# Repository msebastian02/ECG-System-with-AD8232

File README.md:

# ECG-System-with-AD8232

ECG System with STM32F405RGT and AD8232

The system is an interface between an AD8232 and a MCU STM32F405 used to processing, encryption and sending electrocardiography data to a remote server via wifi.

This part was created in Eagle .

Repository Contents

1. Hardware - All Eagle design files (.brd, .sch)

2. Software - MCU Code & WebPageInterface

\*MCU Code - Written and compiled in Keil uVision v5.29

\*WebPageInterface - FrontEnd Written and compiled in Angular 8+ Framework &amp;amp; BackEnd Written and compiled in Python Flask

\*ESP01 Code - Written and compiled in Arduino IDE

3.Documentation

Monograph of the degree project related to the project

Version History

v1.0 Initial Release

License Information

The hardware and code was developed by:

\*Juan Sebastian Munar Aldana

\*Carlos Eduardo Moreno Doria

Electronic engineers from Santo Tomas university, Bogota.

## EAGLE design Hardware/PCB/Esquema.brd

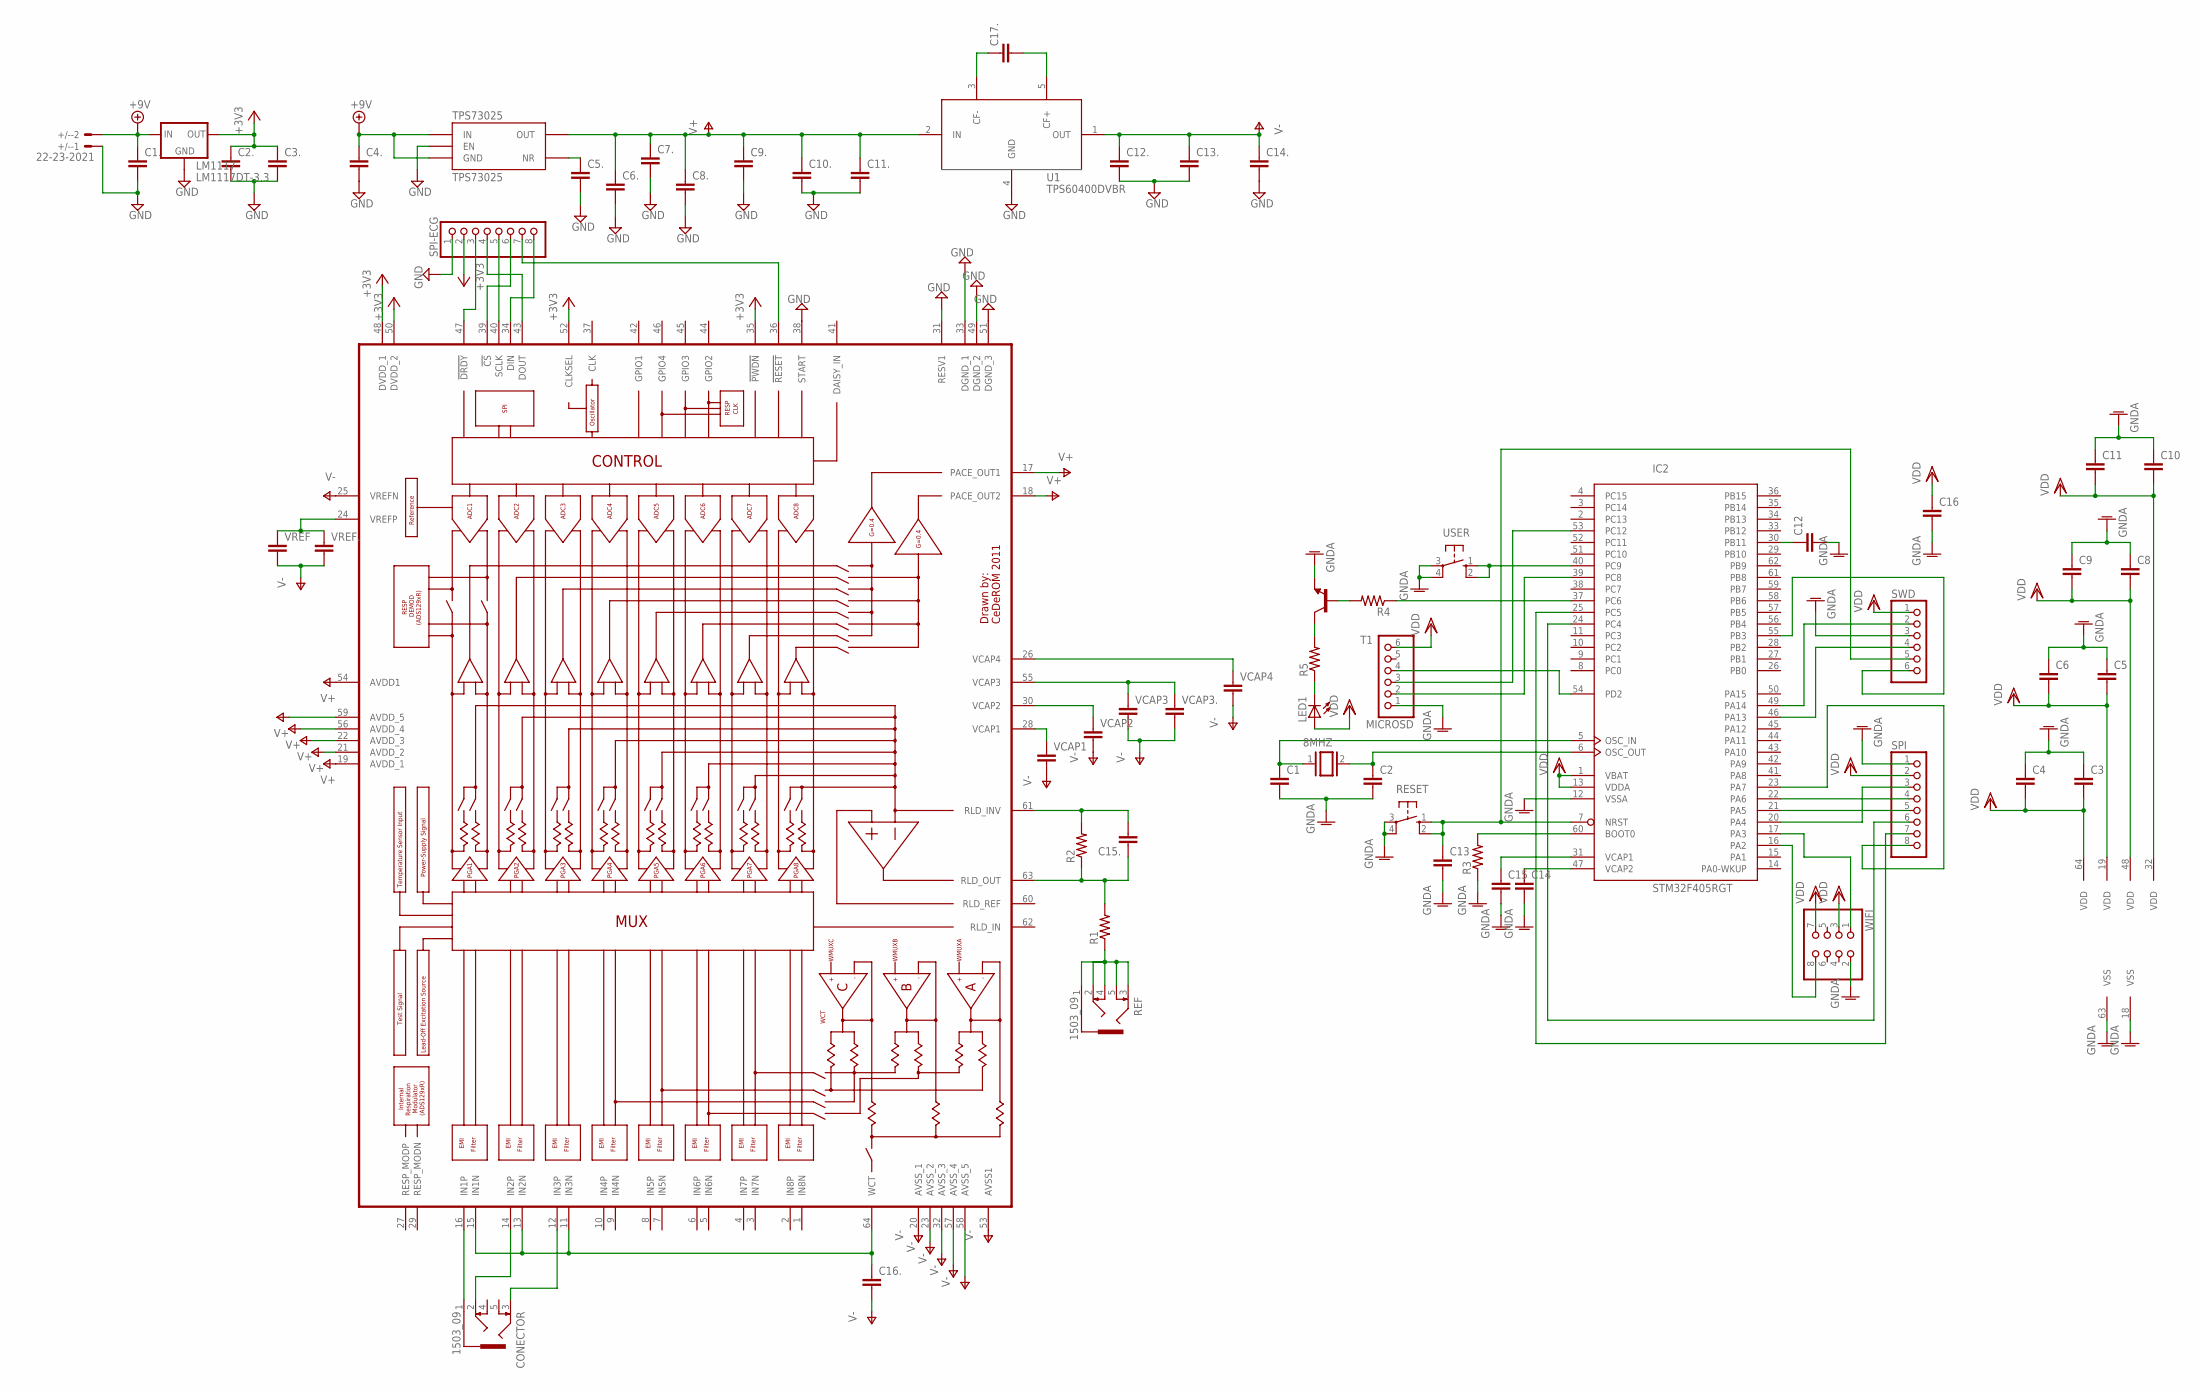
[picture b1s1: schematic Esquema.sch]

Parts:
8MHZ: XTAL/S; QS
+/-: 22-23-2021
C1, C2, C5., C16.: C-EUC0805K; C0805K
C1., C2., C3, C3., C4, C4., C5, C6, C6., C7., C8, C8., C9, C9., C10, C10., C11, C11., C12, C12., C13, C13., C14, C14., C15, C15., C16, C17.: C-EUC1206K; C1206K
CONECTOR: 1503_09
IC2: STM32F405RGT; LQFP64
LED1: LEDCHIP-LED0805; CHIP-LED0805
LM1117: LM1117DT-3.3; TO252
MICROSD: PINHD-1X6; 1X06
R1, R2, R3, R4, R5: R-US_R1206; R1206
REF: 1503_09
RESET: 10-XX; B3F-10XX
SPI: PINHD-1X8; 1X08
SPI-ECG: PINHD-1X8; 1X08
SWD: PINHD-1X6; 1X06
T1: MMBT2222ALT1-NPN-SOT23-BEC; SOT23-BEC
TPS73025: TPS73025; SOT23-5L
U1: TPS60400DVBR; SOT23-5
U$1: ADS1298*PAG*; TQFP64
USER: 10-XX; B3F-10XX
VCAP1: C-EUC0805K; C0805K
VCAP2, VCAP3, VCAP3., VCAP4: C-EUC1206K; C1206K
VREF, VREF.: C-EUC1206K; C1206K
WIFI: PINHD-2X4; 2X04

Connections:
+3V3: C2..1, C3..1, LM1117.3 (OUT), SPI-ECG.2, U$1.35 (!PWDN), U$1.48 (DVDD_1), U$1.50 (DVDD_2), U$1.52 (CLKSEL)
+9V: +/-.2, C1..1, C4..1, LM1117.2 (IN), TPS73025.1 (IN), TPS73025.2 (GND)
GND: +/-.1, C1..2, C2..2, C3..2, C4..2, C5..2, C6..2, C7..2, C8..2, C9..2, C10..2, C11..2, C12..2, C13..2, C14..2, LM1117.1 (GND), SPI-ECG.1, TPS73025.3 (EN), U1.4 (GND), U$1.31 (RESV1), U$1.33 (DGND_1), U$1.38 (START), U$1.49 (DGND_2), U$1.51 (DGND_3)
GNDA: C1.2, C2.2, C3.1, C4.1, C5.1, C6.1, C8.1, C9.1, C10.1, C11.1, C12.2, C13.2, C14.2, C15.2, C16.2, IC2.12 (VSSA), IC2.18 (VSS), IC2.63 (VSS), MICROSD.1, R3.1, RESET.3, RESET.4 (P1), SPI.1, SWD.3, T1.E, USER.3, USER.4 (P1), WIFI.2
unnamed: C17..1, U1.3 (CF-)
unnamed: U$1.24 (VREFP), VREF.1, VREF..1
unnamed: C14.1, IC2.47 (VCAP2)
unnamed: C17..2, U1.5 (CF+)
unnamed: U$1.28 (VCAP1), VCAP1.1
unnamed: C5..1, TPS73025.4 (NR)
unnamed: U$1.30 (VCAP2), VCAP2.1
unnamed: U$1.55 (VCAP3), VCAP3.1, VCAP3..1
unnamed: U$1.26 (VCAP4), VCAP4.1
unnamed: C16..1, U$1.11 (IN3N), U$1.13 (IN2N), U$1.15 (IN1N), U$1.64 (WCT)
unnamed: SPI-ECG.7, U$1.36 (!RESET)
unnamed: SPI-ECG.4, U$1.43 (DOUT)
unnamed: SPI-ECG.5, U$1.40 (SCLK)
unnamed: SPI-ECG.6, U$1.39 (!CS)
unnamed: SPI-ECG.8, U$1.34 (DIN)
unnamed: SPI-ECG.3, U$1.47 (!DRDY)
unnamed: C15..1, R1.2, R2.1, U$1.63 (RLD_OUT)
unnamed: C15..2, R2.2, U$1.61 (RLD_INV)
unnamed: R1.1, REF.1, REF.2, REF.3, REF.4, REF.5
unnamed: CONECTOR.1, U$1.16 (IN1P)
unnamed: CONECTOR.2, U$1.14 (IN2P)
unnamed: CONECTOR.3, U$1.12 (IN3P)
unnamed: 8MHZ.1, C1.1, IC2.5 (OSC_IN)
unnamed: 8MHZ.2, C2.1, IC2.6 (OSC_OUT)
unnamed: IC2.60 (BOOT0), R3.2
unnamed: C12.1, IC2.30 (PB11)
unnamed: C13.1, IC2.7 (NRST), RESET.1 (S), RESET.2 (S1), SWD.5
unnamed: IC2.40 (PC9), USER.1 (S), USER.2 (S1)
unnamed: IC2.22 (PA6), SPI.4
unnamed: IC2.21 (PA5), SPI.5
unnamed: IC2.24 (PC4), SPI.6
unnamed: IC2.25 (PC5), SPI.7
unnamed: IC2.23 (PA7), SPI.8
unnamed: IC2.20 (PA4), SPI.3
unnamed: IC2.49 (PA14), SWD.2
unnamed: IC2.46 (PA13), SWD.4
unnamed: IC2.55 (PB3), SWD.6
unnamed: IC2.39 (PC8), MICROSD.2
unnamed: IC2.53 (PC12), MICROSD.3
unnamed: IC2.54 (PD2), MICROSD.4
unnamed: C15.1, IC2.31 (VCAP1)
unnamed: IC2.16 (PA2), WIFI.8
unnamed: IC2.17 (PA3), WIFI.1
unnamed: R4.2, T1.B
unnamed: IC2.37 (PC6), R4.1
unnamed: R5.2, T1.C
unnamed: LED1.C, R5.1
V+: C6..1, C7..1, C8..1, C9..1, C10..1, C11..1, TPS73025.5 (OUT), U1.2 (IN), U$1.17 (PACE_OUT1), U$1.18 (PACE_OUT2), U$1.19 (AVDD_1), U$1.21 (AVDD_2), U$1.22 (AVDD_3), U$1.54 (AVDD1), U$1.56 (AVDD_4), U$1.59 (AVDD_5)
V-: C12..1, C13..1, C14..1, C16..2, U1.1 (OUT), U$1.20 (AVSS_1), U$1.23 (AVSS_2), U$1.25 (VREFN), U$1.32 (AVSS_3), U$1.53 (AVSS1), U$1.57 (AVSS_4), U$1.58 (AVSS_5), VCAP1.2, VCAP2.2, VCAP3.2, VCAP3..2, VCAP4.2, VREF.2, VREF..2
VDD: C3.2, C4.2, C5.2, C6.2, C8.2, C9.2, C10.2, C11.2, C16.1, IC2.1 (VBAT), IC2.13 (VDDA), IC2.19 (VDD), IC2.32 (VDD), IC2.48 (VDD), IC2.64 (VDD), LED1.A, MICROSD.6, SPI.2, SWD.1, WIFI.3, WIFI.7

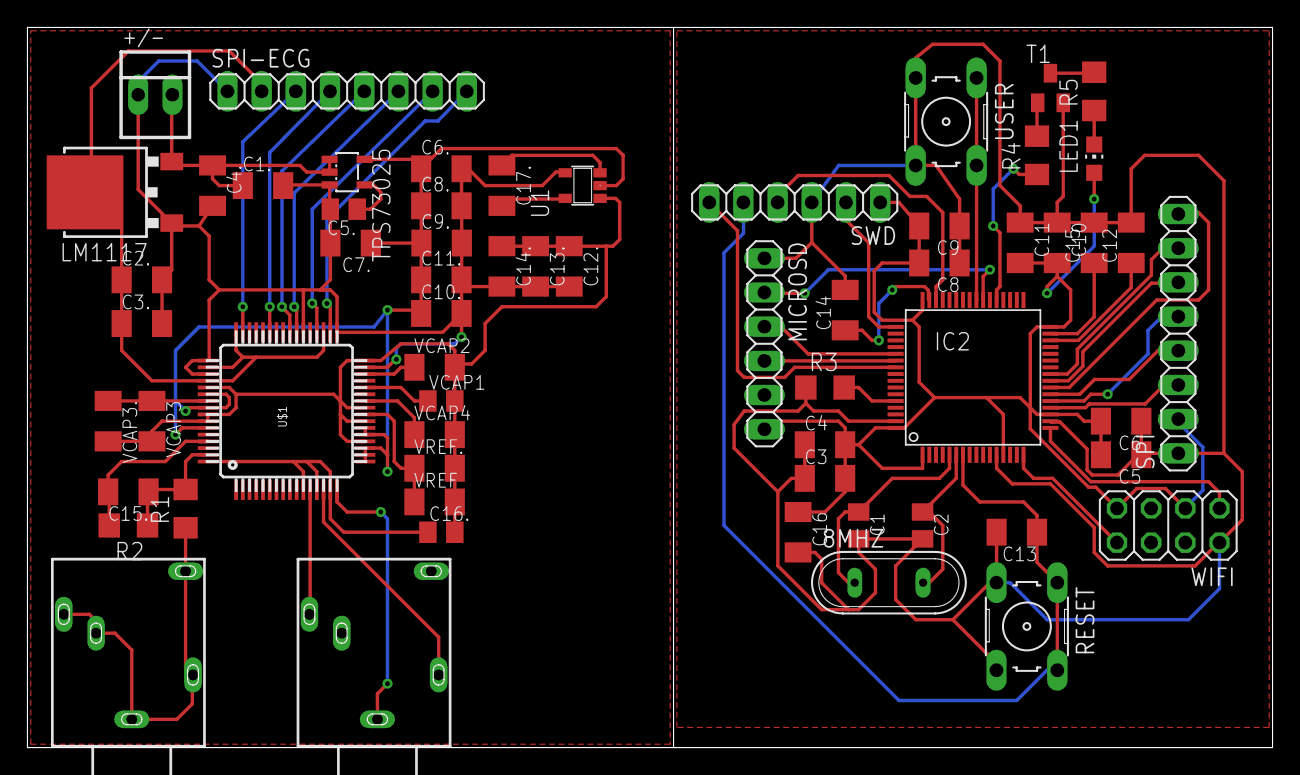
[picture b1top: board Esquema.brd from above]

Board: 2 copper layers, 92.5 x 53.5 mm, 62 parts (0 on the bottom side), 54 nets.

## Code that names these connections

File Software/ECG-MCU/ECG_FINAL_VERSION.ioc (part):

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Mcu.Name=STM32F405RGTx
Mcu.Package=LQFP64
Mcu.UserName=STM32F405RGTx
PA2.Mode=Asynchronous
PA2.Signal=USART2_TX
PA3.Mode=Asynchronous
PA3.Signal=USART2_RX
PA5.Signal=ADCx_IN5
PC12.Mode=SD_1_bit
PC12.Signal=SDIO_CK
PC6.Signal=GPIO_Output
PC8.Mode=SD_1_bit
PC8.Signal=SDIO_D0
PC9.Signal=GPXTI9
PD2.Mode=SD_1_bit
PD2.Signal=SDIO_CMD
RCC.HSE_VALUE=25000000
RCC.SYSCLKFreq_VALUE=16000000
board=ECG_FINAL_VERSION

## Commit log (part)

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2020-05-17 Initial Content
2020-05-17 Bump acorn from 6.4.0 to 6.4.1 in /Software/ECG-Interface/AngularECG
    Bumps [acorn](https://github.com/acornjs/acorn) from 6.4.0 to 6.4.1.
    - [Release notes](https://github.com/acornjs/acorn/releases)
    - [Commits](https://github.com/acornjs/acorn/compare/6.4.0...6.4.1)
2020-06-08 Bump websocket-extensions in /Software/ECG-Interface/AngularECG
    Bumps [websocket-extensions](https://github.com/faye/websocket-extensions-node) from 0.1.3 to 0.1.4.
    - [Release notes](https://github.com/faye/websocket-extensions-node/releases)
    - [Changelog](https://github.com/faye/websocket-extensions-node/blob/master/CHANGELOG.md)
    - [Commits](https://github.com/faye/websocket-extensions-node/compare/0.1.3...0.1.4)
2020-07-08 Bump npm-registry-fetch in /Software/ECG-Interface/AngularECG
    Bumps [npm-registry-fetch](https://github.com/npm/registry-fetch) from 4.0.3 to 4.0.5.
    - [Release notes](https://github.com/npm/registry-fetch/releases)
    - [Changelog](https://github.com/npm/npm-registry-fetch/blob/latest/CHANGELOG.md)
    - [Commits](https://github.com/npm/registry-fetch/commits)
2020-07-20 Bump lodash in /Software/ECG-Interface/AngularECG
    Bumps [lodash](https://github.com/lodash/lodash) from 4.17.15 to 4.17.19.
    - [Release notes](https://github.com/lodash/lodash/releases)
    - [Commits](https://github.com/lodash/lodash/compare/4.17.15...4.17.19)
2020-08-02 Bump elliptic from 6.5.2 to 6.5.3 in /Software/ECG-Interface/AngularECG
    Bumps [elliptic](https://github.com/indutny/elliptic) from 6.5.2 to 6.5.3.
    - [Release notes](https://github.com/indutny/elliptic/releases)
    - [Commits](https://github.com/indutny/elliptic/compare/v6.5.2...v6.5.3)
2020-09-11 Bump http-proxy in /Software/ECG-Interface/AngularECG
    Bumps [http-proxy](https://github.com/http-party/node-http-proxy) from 1.18.0 to 1.18.1.
    - [Release notes](https://github.com/http-party/node-http-proxy/releases)
    - [Changelog](https://github.com/http-party/node-http-proxy/blob/master/CHANGELOG.md)
    - [Commits](https://github.com/http-party/node-http-proxy/compare/1.18.0...1.18.1)
2021-03-10 Bump elliptic from 6.5.2 to 6.5.4 in /Software/ECG-Interface/AngularECG
    Bumps [elliptic](https://github.com/indutny/elliptic) from 6.5.2 to 6.5.4.
    - [Release notes](https://github.com/indutny/elliptic/releases)
    - [Commits](https://github.com/indutny/elliptic/compare/v6.5.2...v6.5.4)
2021-03-31 Bump y18n from 4.0.0 to 4.0.1 in /Software/ECG-Interface/AngularECG
    Bumps [y18n](https://github.com/yargs/y18n) from 4.0.0 to 4.0.1.
    - [Release notes](https://github.com/yargs/y18n/releases)
    - [Changelog](https://github.com/yargs/y18n/blob/master/CHANGELOG.md)
    - [Commits](https://github.com/yargs/y18n/commits)
2021-04-19 Bump ssri from 6.0.1 to 6.0.2 in /Software/ECG-Interface/AngularECG
    Bumps [ssri](https://github.com/npm/ssri) from 6.0.1 to 6.0.2.
    - [Release notes](https://github.com/npm/ssri/releases)
    - [Changelog](https://github.com/npm/ssri/blob/v6.0.2/CHANGELOG.md)
    - [Commits](https://github.com/npm/ssri/compare/v6.0.1...v6.0.2)
2021-05-06 Bump highcharts in /Software/ECG-Interface/AngularECG
    Bumps [highcharts](https://github.com/highcharts/highcharts-dist) from 8.0.4 to 9.0.0.
    - [Release notes](https://github.com/highcharts/highcharts-dist/releases)
    - [Commits](https://github.com/highcharts/highcharts-dist/compare/v8.0.4...v9.0.0)
2021-05-09 Bump url-parse from 1.4.7 to 1.5.1 in /Software/ECG-Interface/AngularECG
    Bumps [url-parse](https://github.com/unshiftio/url-parse) from 1.4.7 to 1.5.1.
    - [Release notes](https://github.com/unshiftio/url-parse/releases)
    - [Commits](https://github.com/unshiftio/url-parse/compare/1.4.7...1.5.1)
2021-05-11 Bump lodash in /Software/ECG-Interface/AngularECG
    Bumps [lodash](https://github.com/lodash/lodash) from 4.17.15 to 4.17.21.
    - [Release notes](https://github.com/lodash/lodash/releases)
    - [Commits](https://github.com/lodash/lodash/compare/4.17.15...4.17.21)
2021-05-28 Bump dns-packet in /Software/ECG-Interface/AngularECG
    Bumps [dns-packet](https://github.com/mafintosh/dns-packet) from 1.3.1 to 1.3.4.
    - [Release notes](https://github.com/mafintosh/dns-packet/releases)
    - [Changelog](https://github.com/mafintosh/dns-packet/blob/master/CHANGELOG.md)
    - [Commits](https://github.com/mafintosh/dns-packet/compare/v1.3.1...v1.3.4)
2021-08-04 Bump tar from 4.4.13 to 4.4.15 in /Software/ECG-Interface/AngularECG
    Bumps [tar](https://github.com/npm/node-tar) from 4.4.13 to 4.4.15.
    - [Release notes](https://github.com/npm/node-tar/releases)
    - [Changelog](https://github.com/npm/node-tar/blob/main/CHANGELOG.md)
    - [Commits](https://github.com/npm/node-tar/compare/v4.4.13...v4.4.15)
    ---
    updated-dependencies:
2021-08-12 Bump path-parse in /Software/ECG-Interface/AngularECG
    Bumps [path-parse](https://github.com/jbgutierrez/path-parse) from 1.0.6 to 1.0.7.
    - [Release notes](https://github.com/jbgutierrez/path-parse/releases)
    - [Commits](https://github.com/jbgutierrez/path-parse/commits/v1.0.7)
    ---
    updated-dependencies:
    - dependency-name: path-parse
2021-09-02 Bump tar from 4.4.13 to 4.4.19 in /Software/ECG-Interface/AngularECG
    Bumps [tar](https://github.com/npm/node-tar) from 4.4.13 to 4.4.19.
    - [Release notes](https://github.com/npm/node-tar/releases)
    - [Changelog](https://github.com/npm/node-tar/blob/main/CHANGELOG.md)
    - [Commits](https://github.com/npm/node-tar/compare/v4.4.13...v4.4.19)
    ---
    updated-dependencies:
2022-01-14 Bump follow-redirects in /Software/ECG-Interface/AngularECG
    Bumps [follow-redirects](https://github.com/follow-redirects/follow-redirects) from 1.10.0 to 1.14.7.
    - [Release notes](https://github.com/follow-redirects/follow-redirects/releases)
    - [Commits](https://github.com/follow-redirects/follow-redirects/compare/v1.10.0...v1.14.7)
    ---
    updated-dependencies:
    - dependency-name: follow-redirects
2022-02-11 Bump karma from 4.3.0 to 6.3.14 in /Software/ECG-Interface/AngularECG
    Bumps [karma](https://github.com/karma-runner/karma) from 4.3.0 to 6.3.14.
    - [Release notes](https://github.com/karma-runner/karma/releases)
    - [Changelog](https://github.com/karma-runner/karma/blob/master/CHANGELOG.md)
    - [Commits](https://github.com/karma-runner/karma/compare/v4.3.0...v6.3.14)
    ---
    updated-dependencies:
2022-02-13 Bump follow-redirects in /Software/ECG-Interface/AngularECG
    Bumps [follow-redirects](https://github.com/follow-redirects/follow-redirects) from 1.10.0 to 1.14.8.
    - [Release notes](https://github.com/follow-redirects/follow-redirects/releases)
    - [Commits](https://github.com/follow-redirects/follow-redirects/compare/v1.10.0...v1.14.8)
    ---
    updated-dependencies:
    - dependency-name: follow-redirects
2022-02-19 Bump url-parse from 1.4.7 to 1.5.7 in /Software/ECG-Interface/AngularECG
    Bumps [url-parse](https://github.com/unshiftio/url-parse) from 1.4.7 to 1.5.7.
    - [Release notes](https://github.com/unshiftio/url-parse/releases)
    - [Commits](https://github.com/unshiftio/url-parse/compare/1.4.7...1.5.7)
    ---
    updated-dependencies:
    - dependency-name: url-parse
2022-02-27 Bump url-parse in /Software/ECG-Interface/AngularECG
    Bumps [url-parse](https://github.com/unshiftio/url-parse) from 1.4.7 to 1.5.10.
    - [Release notes](https://github.com/unshiftio/url-parse/releases)
    - [Commits](https://github.com/unshiftio/url-parse/compare/1.4.7...1.5.10)
    ---
    updated-dependencies:
    - dependency-name: url-parse
2022-04-29 Bump async from 2.6.3 to 2.6.4 in /Software/ECG-Interface/AngularECG
    Bumps [async](https://github.com/caolan/async) from 2.6.3 to 2.6.4.
    - [Release notes](https://github.com/caolan/async/releases)
    - [Changelog](https://github.com/caolan/async/blob/v2.6.4/CHANGELOG.md)
    - [Commits](https://github.com/caolan/async/compare/v2.6.3...v2.6.4)
    ---
    updated-dependencies:
2022-06-01 Bump eventsource in /Software/ECG-Interface/AngularECG
    Bumps [eventsource](https://github.com/EventSource/eventsource) from 1.0.7 to 1.1.1.
    - [Release notes](https://github.com/EventSource/eventsource/releases)
    - [Changelog](https://github.com/EventSource/eventsource/blob/master/HISTORY.md)
    - [Commits](https://github.com/EventSource/eventsource/compare/v1.0.7...v1.1.1)
    ---
    updated-dependencies:
2022-06-03 Bump @angular/core in /Software/ECG-Interface/AngularECG
    Bumps [@angular/core](https://github.com/angular/angular/tree/HEAD/packages/core) from 9.0.2 to 11.0.5.
    - [Release notes](https://github.com/angular/angular/releases)
    - [Changelog](https://github.com/angular/angular/blob/main/CHANGELOG.md)
    - [Commits](https://github.com/angular/angular/commits/11.0.5/packages/core)
    ---
    updated-dependencies:
2022-09-08 Bump jszip from 3.2.2 to 3.10.1 in /Software/ECG-Interface/AngularECG
    Bumps [jszip](https://github.com/Stuk/jszip) from 3.2.2 to 3.10.1.
    - [Release notes](https://github.com/Stuk/jszip/releases)
    - [Changelog](https://github.com/Stuk/jszip/blob/main/CHANGES.md)
    - [Commits](https://github.com/Stuk/jszip/compare/v3.2.2...v3.10.1)
    ---
    updated-dependencies:
2022-11-19 Bump loader-utils and @angular-devkit/build-angular
    Bumps [loader-utils](https://github.com/webpack/loader-utils) to 3.2.1 and updates ancestor dependency [@angular-devkit/build-angular](https://github.com/angular/angular-cli). These dependencies need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
    Updates `loader-utils` from 1.2.3 to 3.2.1
    - [Release notes](https://github.com/webpack/loader-utils/releases)
    - [Changelog](https://github.com/webpack/loader-utils/blob/master/CHANGELOG.md)
    - [Commits](https://github.com/webpack/loader-utils/compare/v1.2.3...v3.2.1)
    Updates `@angular-devkit/build-angular` from 0.900.3 to 15.0.0
2022-11-23 Bump engine.io and karma in /Software/ECG-Interface/AngularECG
    Bumps [engine.io](https://github.com/socketio/engine.io) to 6.2.1 and updates ancestor dependency [karma](https://github.com/karma-runner/karma). These dependencies need to be updated together.
    Updates `engine.io` from 3.2.1 to 6.2.1
    - [Release notes](https://github.com/socketio/engine.io/releases)
    - [Changelog](https://github.com/socketio/engine.io/blob/main/CHANGELOG.md)
    - [Commits](https://github.com/socketio/engine.io/compare/3.2.1...6.2.1)
    Updates `karma` from 4.3.0 to 6.4.1
2022-12-11 Bump qs from 6.5.2 to 6.5.3 in /Software/ECG-Interface/AngularECG
    Bumps [qs](https://github.com/ljharb/qs) from 6.5.2 to 6.5.3.
    - [Release notes](https://github.com/ljharb/qs/releases)
    - [Changelog](https://github.com/ljharb/qs/blob/main/CHANGELOG.md)
    - [Commits](https://github.com/ljharb/qs/compare/v6.5.2...v6.5.3)
    ---
    updated-dependencies:
2022-12-12 Bump express from 4.17.1 to 4.18.2 in /Software/ECG-Interface/AngularECG
    Bumps [express](https://github.com/expressjs/express) from 4.17.1 to 4.18.2.
    - [Release notes](https://github.com/expressjs/express/releases)
    - [Changelog](https://github.com/expressjs/express/blob/master/History.md)
    - [Commits](https://github.com/expressjs/express/compare/4.17.1...4.18.2)
    ---
    updated-dependencies:
2023-01-01 Bump json5 and @angular-devkit/build-angular
    Bumps [json5](https://github.com/json5/json5) to 2.2.3 and updates ancestor dependency [@angular-devkit/build-angular](https://github.com/angular/angular-cli). These dependencies need to be updated t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
    Updates `json5` from 2.1.2 to 2.2.3
    - [Release notes](https://github.com/json5/json5/releases)
    - [Changelog](https://github.com/json5/json5/blob/main/CHANGELOG.md)
    - [Commits](https://github.com/json5/json5/compare/v2.1.2...v2.2.3)
    Updates `@angular-devkit/build-angular` from 0.900.3 to 15.0.4
